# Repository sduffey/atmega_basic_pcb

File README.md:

# ATMEGA328P Basic PCB for Eagle CAD

Schematic and PCB files for a basic example of an ATMEGA328P (Arduino Uno) using cadsoft's EagleCAD. The purpose is of this is just to help first time PCB makers start with a basic example.

The board needs to be externally powered with ~9volts DC, you can use either a L4931-5.0 (available at adafruit) or an LM7805 voltage regulator. Either one needs to be TO-92 format/size.

The schematic is meant to be fairly generic, there is a potentiometer that can be read on analog pin 0. LEDS are on pins 3, 5, 6, 9, 10, 11

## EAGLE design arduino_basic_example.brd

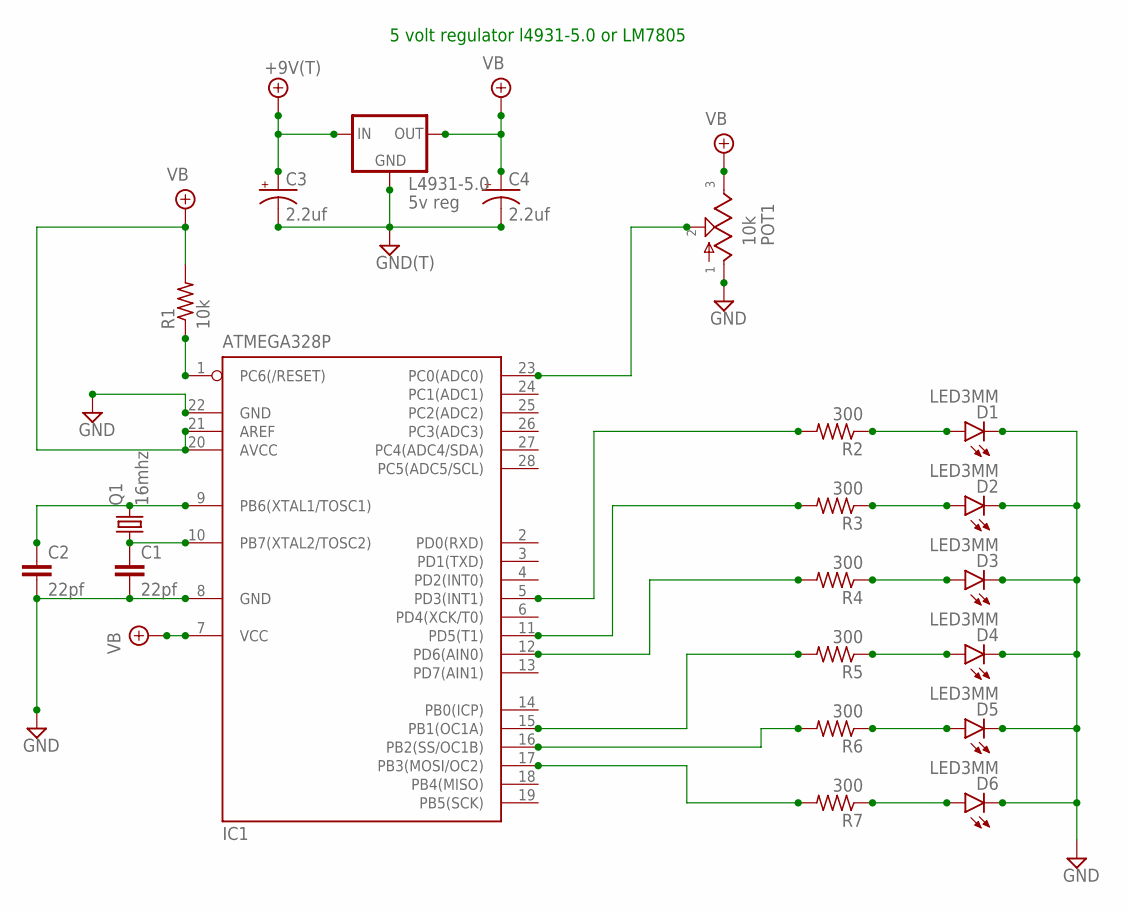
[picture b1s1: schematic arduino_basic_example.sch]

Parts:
+9V1: +9V(T); SQUARE
C1, C2: 22pf; 050X030_025
C3, C4: 2.2uf; 050_020
D1, D2, D3, D4, D5, D6: LED3MM
GND1: GND(T); SQUARE
IC1: ATMEGA328P; DIL28-3
L4931-5.0: 5v reg; 78LXX
POT1: 10k; 16MM
Q1: 16mhz; HC49/S
R1: 10k; R0207/3
R2, R3, R4, R5, R6, R7: 300; R0207/3

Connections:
+9V: +9V1.1, C3.+, L4931-5.0.IN
GND: C1.2, C2.2, C3.-, C4.-, D1.K (C), D2.K (C), D3.K (C), D4.K (C), D5.K (C), D6.K (C), GND1.1, IC1.8 (GND), IC1.22 (GND), L4931-5.0.GND, POT1.1
unnamed: IC1.5 (PD3(INT1)), R2.2
unnamed: C2.1, IC1.9 (PB6(XTAL1/TOSC1)), Q1.2
unnamed: C1.1, IC1.10 (PB7(XTAL2/TOSC2)), Q1.1
unnamed: IC1.11 (PD5(T1)), R3.2
unnamed: IC1.1 (PC6(/RESET)), R1.1
unnamed: IC1.12 (PD6(AIN0)), R4.2
unnamed: IC1.15 (PB1(OC1A)), R5.2
unnamed: D1.A, R2.1
unnamed: IC1.16 (PB2(SS/OC1B)), R6.2
unnamed: IC1.17 (PB3(MOSI/OC2)), R7.2
unnamed: D2.A, R3.1
unnamed: D3.A, R4.1
unnamed: D4.A, R5.1
unnamed: D5.A, R6.1
unnamed: D6.A, R7.1
unnamed: IC1.23 (PC0(ADC0)), POT1.2
VB: C4.+, IC1.7 (VCC), IC1.20 (AVCC), IC1.21 (AREF), L4931-5.0.OUT, POT1.3, R1.2

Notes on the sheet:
5 volt regulator l4931-5.0 or LM7805

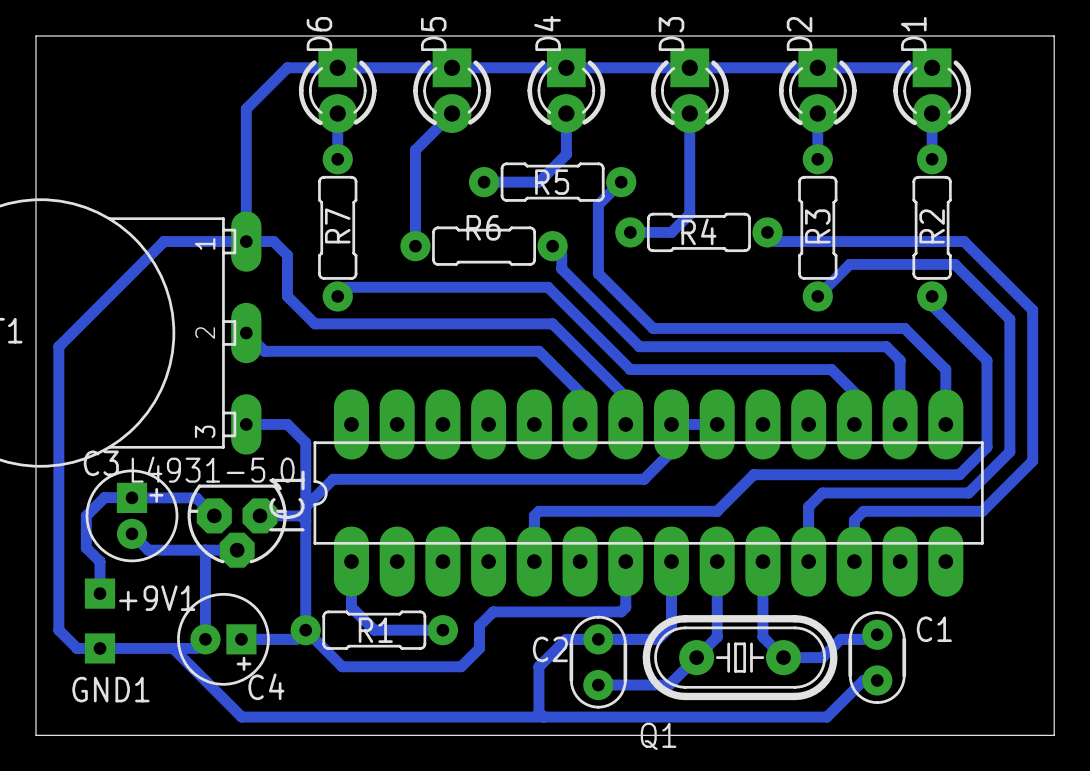
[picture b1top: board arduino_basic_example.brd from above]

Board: 2 copper layers, 56.6 x 38.9 mm, 23 parts (0 on the bottom side), 19 nets.

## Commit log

2015-10-16 basic Eagle ATMEGA pcb example
2015-10-16 update regulator label
